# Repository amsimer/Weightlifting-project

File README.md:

# Power Cable V2

Technology and Health Project Course

MSc Sports Technology Students at KTH Royal Institute of Technology

# Product Information

This product is an electric weight lifting device that can be set to different weights digitally without the need for external accesories like weight plates. The device can be operated through an app in IOS systems and a HTML file with any operating system in a PC. The user is able to set the desired training weight, see the current force in Kg they are pulling with, and see the speed for every rep. It also has an alternative adaptive resistance mode, for which the user selects their desired rep speed and the device automatically makes every rep close to muscle failure to optimize hyperthrophy training.

## Hardware

The device uses an electric longboard's ODrive motor, that attempts to go back to its starting position once turned on. The set weight is converted into a max current that limits with how much force can the motor pull back to return to its position. 

The hardware improvements made to the Power Cable previous prototype involved adding a cable box to enclose the power supply, Odrive controller, and Bluetooth antenna with an MDF box to avoid safety hazards related to cables coming from the power supply to the motor being exposed to the environment.

The box was designed using the open-source boxes.py tool and Inkscape to draw the cable holes. The dimensions were: 240x130x110 millimeters, and the cable holes in the front of the box are 40mm in diameter, and the back hole is 70 millimeters in diameter. 

- See all the hardware files here: [Hardware](https://github.com/amsimer/Weightlifting-project/tree/main/Hardware).
- View the PCB design and manufacturing files here: [PCB files](Hardware/PCB/).

## Software

The software provides three interfaces for operating, testing and monitoring the device.

### Original HTML interface

The original JavaScript interface controls the device through a computer. It was adapted from the earlier Python implementation and provides fixed-weight and adaptive-resistance modes together with force and speed tracking. It can be operated directly from this Github page.

- [Open the HTML interface](https://amsimer.github.io/Weightlifting-project/Software/control.html)

#### Demostration

https://github.com/user-attachments/assets/4b4825d2-2c79-4780-979c-93d6ef282277

https://github.com/user-attachments/assets/1ee684fa-d978-47a7-b3ad-fbba4a475636

### iOS application (Bluetooth Low Energy)

The native SwiftUI iPhone application connects directly to the ESP32-C3 over Bluetooth Low Energy. It supports motor calibration, resistance selection, target sets and repetitions, start/stop control, cable return, live cable speed, repetition and set tracking, set timing, last-repetition statistics, adaptive next-set recommendations and spoken/audio feedback.

- [Open the iOS application source](Software/iOS-APP/)
#### Demonstration

https://github.com/user-attachments/assets/164f28de-e329-4bf6-b57f-8a9462edd9ee

### Wi-Fi training dashboard

The ESP32 creates the local `POWER-CABLE` Wi-Fi network and serves a browser dashboard from its LittleFS filesystem. The dashboard provides browser-based workout control and live feedback without requiring an installed application. It displays connection state, repetitions, set progress, cable speed, set time, last-repetition measurements and the next-set recommendation.

- [Open the live POWER-CABLE dashboard](http://192.168.4.1/) — available while connected to the `POWER-CABLE` Wi-Fi network
- [View the Wi-Fi dashboard source](Software/WiFi-Dashboard/)
#### Demonstration

https://github.com/user-attachments/assets/2d418f85-5986-48f9-bc50-d3956d41b557

### ESP32 firmware

The shared Arduino firmware connects both wireless interfaces to the ODrive motor controller. It handles BLE commands, HTTP requests, LittleFS-hosted web files, ODrive UART communication, calibration, cable position and velocity measurements, repetition detection, workout state and safety-related motor-stop commands.

- [Open the ESP32 firmware](Software/Firmware/WeightLifting_ODrive_RepTracking/)

Before creating the HTML and iOS interfaces, two Python programs were used to verify that the device could be operated from Windows and macOS. These earlier development and diagnostic files are retained in the repository.

- [Browse all software files](Software/)

## Documentation

In this folder you can find relevant documents for this project, including the short paper and lean canvas.

- Find it here: [Documents](https://github.com/amsimer/Weightlifting-project/tree/main/Docs).

There's also a data folder where you can find the data used to validate the speed tracking for the HTML interface, as well as data extracted from the app.

- Look here: [Data](https://github.com/amsimer/Weightlifting-project/tree/main/Data).

## Previous Work

The device was originally built by Linus Remahl, research engineer at KTH, Stockholm, Sweden.

- Find his Github profile here: [Linus](https://github.com/linusreM).

Then it was worked on and improved by a group of third year students for Medical Engineering at KTH. You can look at their work in the following:

- Github Repository: [Power Cable](https://github.com/HugoPersson01/POWER-CABLE).
- Previous work files: [Previous Work](https://github.com/amsimer/Weightlifting-project/tree/main/Previous_Work).

## Contributors

<a href="https://github.com/amsimer">
  <b>Santiago Remis: amsimer</b><br>
  <br>
</a>

<a href="https://github.com/euro311">
  <b>Eusebio Rodriguez: euro311</b><br>
  <br>
</a>

<a href="https://github.com/Yunus-Sah">
  <b>Yunus Emre Sahin: Yunus-Sah</b><br>
  <br>
</a>

<a href="https://github.com/shaunvarghese">
  <b>Shaun Varghese: shaunvarghese</b><br>
  <br>
</a>

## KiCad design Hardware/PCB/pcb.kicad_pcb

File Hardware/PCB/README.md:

# PCB files

This folder contains the KiCad design files and fabrication outputs for the POWER CABLE V2 printed circuit board.

## Design files

- `pcb.kicad_pro` — KiCad project
- `pcb.kicad_sch` — schematic
- `pcb.kicad_pcb` — PCB layout

## Manufacturing files

The `Manufacturing/` folder contains the Gerber, drill and job files required by a PCB manufacturer.

Review the fabrication settings and board specifications with the selected manufacturer before ordering.

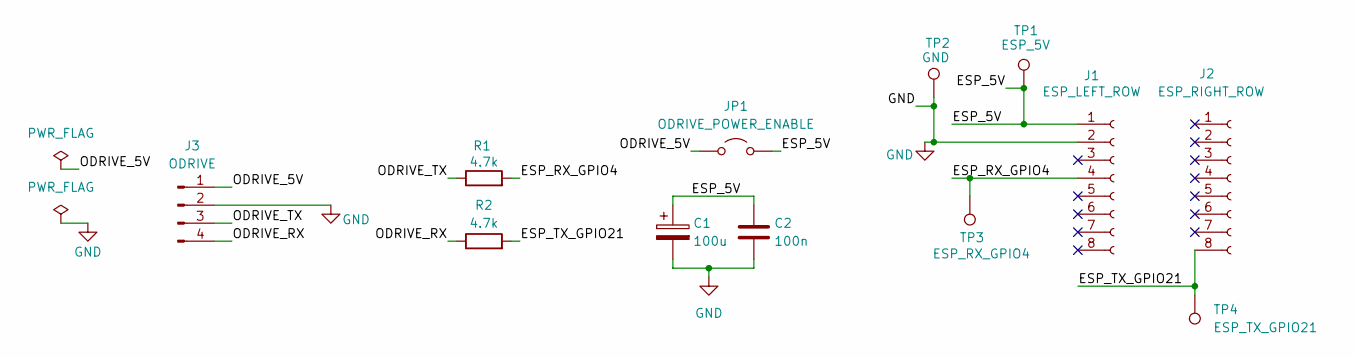
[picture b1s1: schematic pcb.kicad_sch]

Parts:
C1: 100u; CP_Radial_D5.0mm_P2.00mm
C2: 100n; C_Disc_D5.0mm_W2.5mm_P5.00mm
J1: ESP_LEFT_ROW; PinSocket_1x08_P2.54mm_Vertical
J2: ESP_RIGHT_ROW; PinSocket_1x08_P2.54mm_Vertical
J3: ODRIVE; TerminalBlock_4Ucon_1x04_P3.50mm_Horizontal
JP1: ODRIVE_POWER_ENABLE; PinHeader_1x02_P2.54mm_Vertical
R1, R2: 4.7k; R_Axial_DIN0207_L6.3mm_D2.5mm_P10.16mm_Horizontal
TP1: ESP_5V; PinHeader_1x01_P2.54mm_Vertical
TP2: GND; PinHeader_1x01_P2.54mm_Vertical
TP3: ESP_RX_GPIO4; PinHeader_1x01_P2.54mm_Vertical
TP4: ESP_TX_GPIO21; PinHeader_1x01_P2.54mm_Vertical

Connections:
/ESP_5V: C1.1, C2.2, J1.1, JP1.2 (B), TP1.1 (1_1)
/ESP_RX_GPIO4: J1.4, R1.2, TP3.1 (1_1)
/ESP_TX_GPIO21: J2.8 (Pin_8_8), R2.2, TP4.1 (1_1)
/ODRIVE_5V: J3.1, JP1.1 (A)
/ODRIVE_RX: J3.4, R2.1
/ODRIVE_TX: J3.3, R1.1
GND: C1.2, C2.1, J1.2, J3.2, TP2.1 (1_1)

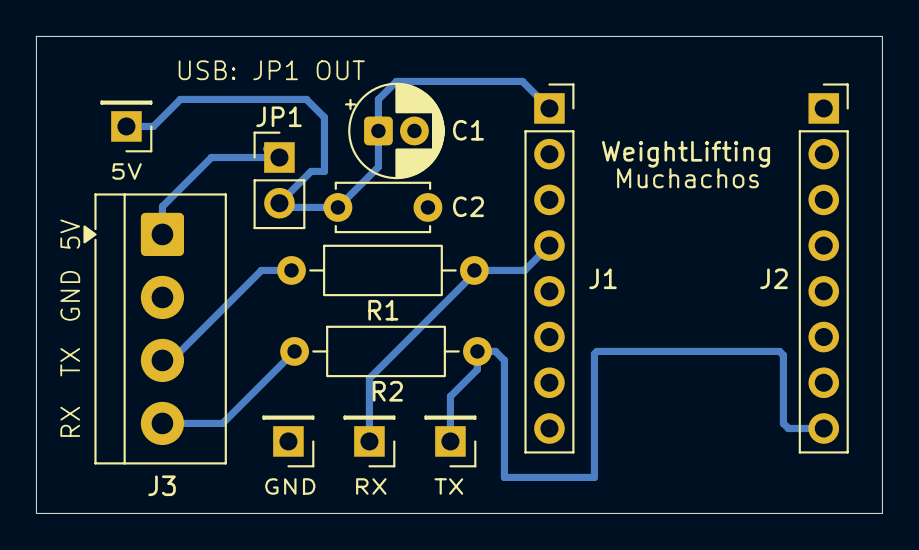
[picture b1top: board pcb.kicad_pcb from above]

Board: 2 copper layers, 47.0 x 26.5 mm, 12 parts (0 on the bottom side), 7 nets.
